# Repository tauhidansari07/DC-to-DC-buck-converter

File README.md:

# DC to DC Buck Converter

A Simple but capable DC to DC Step down Converter range voltage Input Voltage Range: 3.8V to 40V and Output Voltage Range: 0.8V to ~19V 

## Technical Details
* **Core IC:** AP64501SP-13 Step down IC
* **Design Software:** KiCad 
* **Key Features:** A variable Step Down DC to DC Buck Converter 

## Included Files
* KiCad source files (Schematic & PCB layout)
* PDF Schematic for quick viewing
* Ready-to-manufacture Gerber files

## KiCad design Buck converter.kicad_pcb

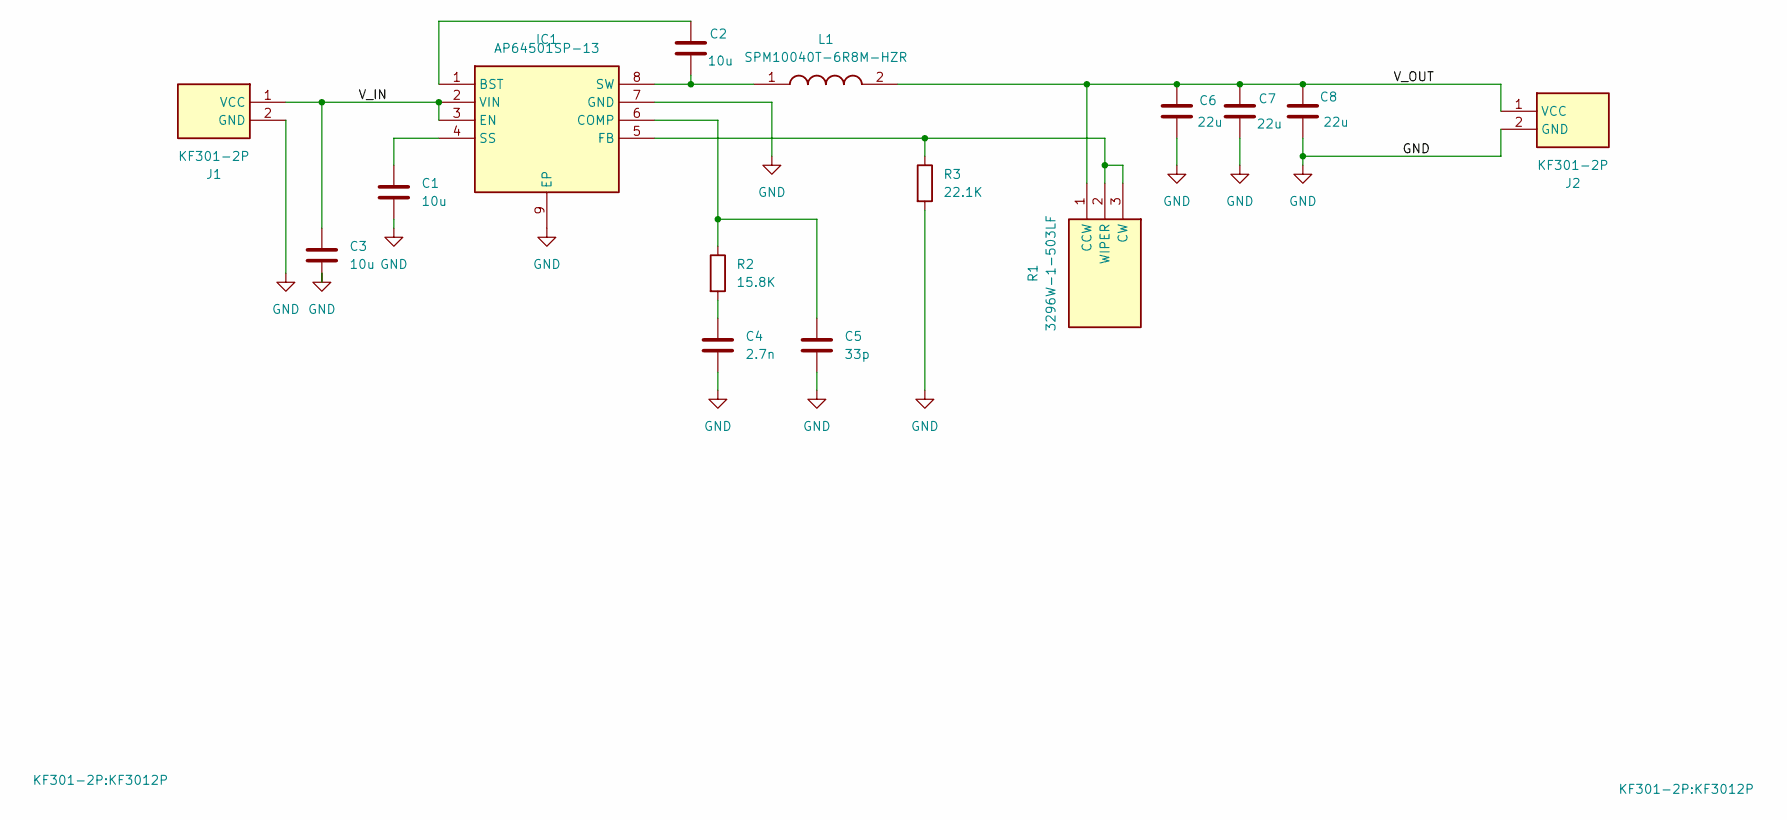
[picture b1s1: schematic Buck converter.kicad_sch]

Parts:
C1, C2, C3: 10u; C_0603_1608Metric
C4: 2.7n; C_0402_1005Metric_Pad0.74x0.62mm_HandSolder
C5: 33p; C_0402_1005Metric_Pad0.74x0.62mm_HandSolder
C6, C7, C8: 22u; C_0805_2012Metric_Pad1.18x1.45mm_HandSolder
IC1: AP64501SP-13; SOIC127P600X163-9N; Manufacturer_Part_Number AP64501SP-13; Mouser Part Number 621-AP64501SP-13
J1, J2: KF301-2P; KF3012P; Manufacturer_Part_Number KF301-2P
L1: SPM10040T-6R8M-HZR; SPM10040T6R8MHZR; Manufacturer_Part_Number SPM10040T-6R8M-HZR; Mouser Part Number 810-SPM100406R8MHZR
R1: 3296W-1-503LF; 3296W1503LF; Manufacturer_Part_Number 3296W-1-503LF; Mouser Part Number 652-3296W-1-503LF
R2: 15.8K; R_0402_1005Metric_Pad0.72x0.64mm_HandSolder
R3: 22.1K; R_0402_1005Metric_Pad0.72x0.64mm_HandSolder

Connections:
/V_IN: C3.1, IC1.2 (VIN), IC1.3 (EN), J1.1 (VCC)
/V_OUT: C6.1, C7.1, C8.1, J2.1 (VCC), L1.2, R1.1 (CCW)
GND: C1.2, C3.2, C4.2, C5.2, C6.2, C7.2, C8.2, IC1.7 (GND), IC1.9 (EP), J1.2 (GND), J2.2 (GND), R3.2
unnamed: C4.1, R2.2
unnamed: C2.1, IC1.1 (BST)
unnamed: C5.1, IC1.6 (COMP), R2.1
unnamed: IC1.5 (FB), R1.2 (WIPER), R1.3 (CW), R3.1
unnamed: C1.1, IC1.4 (SS)
unnamed: C2.2, IC1.8 (SW), L1.1

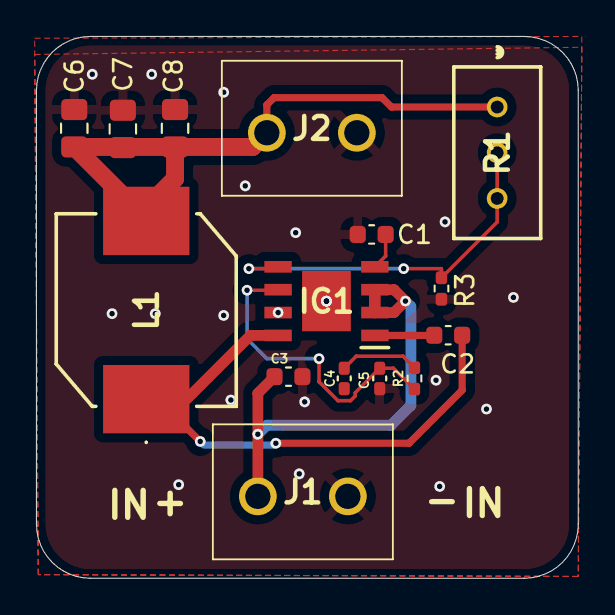
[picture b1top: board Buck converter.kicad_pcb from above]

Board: 2 copper layers, 30.1 x 30.1 mm, 15 parts (0 on the bottom side), 9 nets.
